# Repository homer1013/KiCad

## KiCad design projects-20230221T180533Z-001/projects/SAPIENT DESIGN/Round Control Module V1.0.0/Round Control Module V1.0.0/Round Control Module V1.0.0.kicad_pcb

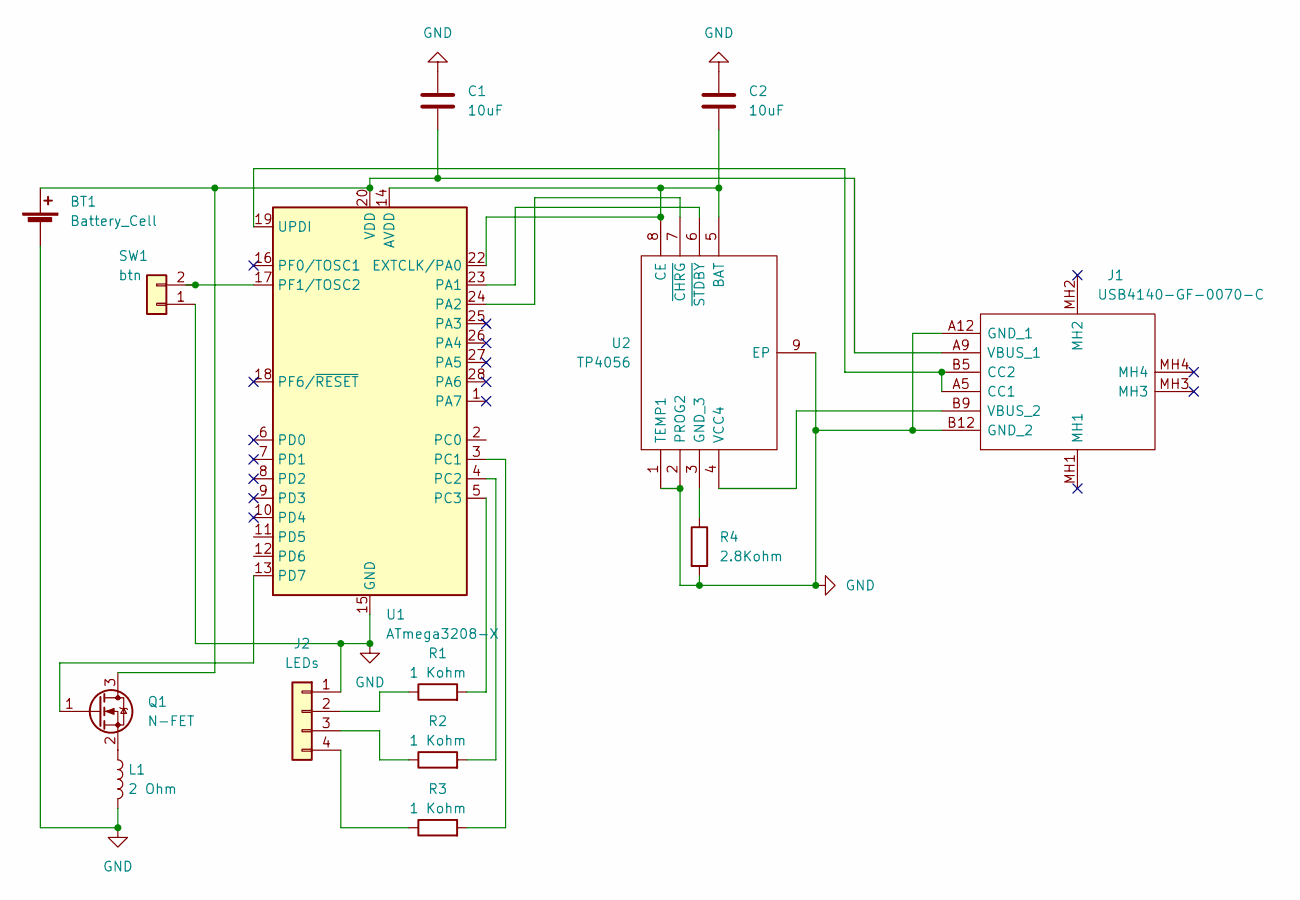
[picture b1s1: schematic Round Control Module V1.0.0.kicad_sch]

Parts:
BT1: Battery_Cell; PinHeader_1x02_P2.54mm_Vertical
C1, C2: 10uF; C_0603_1608Metric_Pad1.08x0.95mm_HandSolder
J1: USB4140-GF-0070-C; USB4140GF0070C; Mouser Part Number 640-USB4140-GF-0070C
J2: LEDs; PinHeader_1x04_P2.54mm_Vertical
L1: 2 Ohm; L_Axial_L6.6mm_D2.7mm_P2.54mm_Vertical_Vishay_IM-2
Q1: N-FET; SOT-23
R1, R2, R3: 1 Kohm; R_0603_1608Metric_Pad0.98x0.95mm_HandSolder
R4: 2.8Kohm; R_0603_1608Metric_Pad0.98x0.95mm_HandSolder
SW1: btn; PinHeader_1x02_P2.54mm_Vertical
U1: ATmega3208-X; SSOP-28_5.3x10.2mm_P0.65mm
U2: TP4056; SOIC-8-1EP_3.9x4.9mm_P1.27mm_EP2.514x3.2mm_ThermalVias; Manufacturer_Part_Number TP4056

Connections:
GND: BT1.2 (-), C1.1, C2.1, J1.A12 (GND_1), J1.B12 (GND_2), J2.1, L1.2, R4.2, SW1.1, U1.15 (GND), U1.21 (GND), U2.1 (TEMP1), U2.2 (PROG2), U2.9 (EP)
unnamed: BT1.1 (+), C1.2, J1.A9 (VBUS_1), Q1.3 (D), U1.20 (VDD)
unnamed: C2.2, U1.14 (AVDD), U1.22 (EXTCLK/PA0), U2.5 (BAT), U2.8 (CE)
unnamed: J2.2, R1.1
unnamed: J2.3, R2.1
unnamed: J2.4, R3.1
unnamed: L1.1, Q1.2 (S)
unnamed: Q1.1 (G), U1.13 (PD7)
unnamed: R1.2, U1.5 (PC3)
unnamed: R2.2, U1.4 (PC2)
unnamed: R3.2, U1.3 (PC1)
unnamed: R4.1, U2.3 (GND_3)
unnamed: SW1.2, U1.17 (PF1/TOSC2)
unnamed: J1.A5 (CC1), J1.B5 (CC2), U1.19 (UPDI)
unnamed: U1.23 (PA1), U2.6 (~STDBY)
unnamed: U1.24 (PA2), U2.7 (~CHRG)
unnamed: J1.B9 (VBUS_2), U2.4 (VCC4)

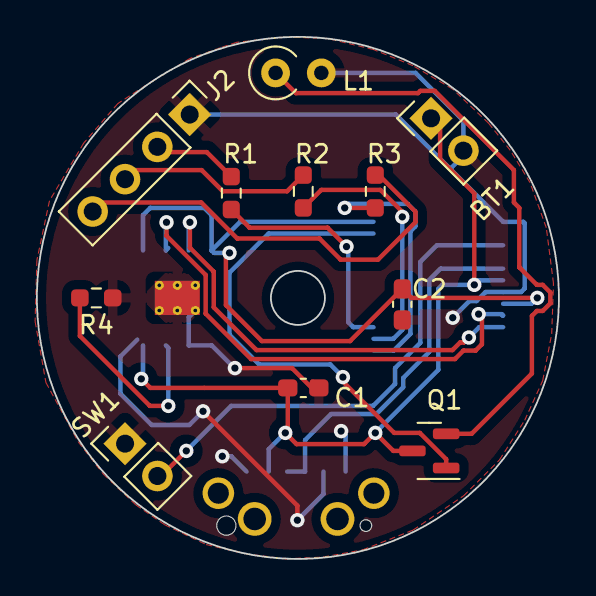
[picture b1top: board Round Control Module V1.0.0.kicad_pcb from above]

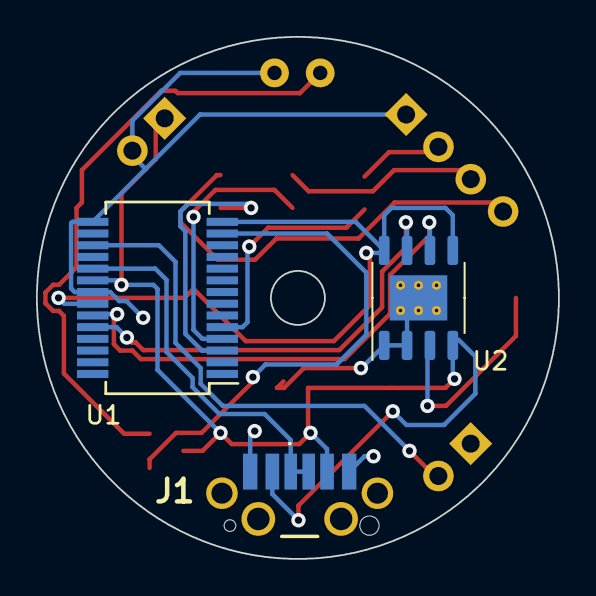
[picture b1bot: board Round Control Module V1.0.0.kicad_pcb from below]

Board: 2 copper layers, 29.0 x 29.0 mm, 14 parts (3 on the bottom side), 17 nets.

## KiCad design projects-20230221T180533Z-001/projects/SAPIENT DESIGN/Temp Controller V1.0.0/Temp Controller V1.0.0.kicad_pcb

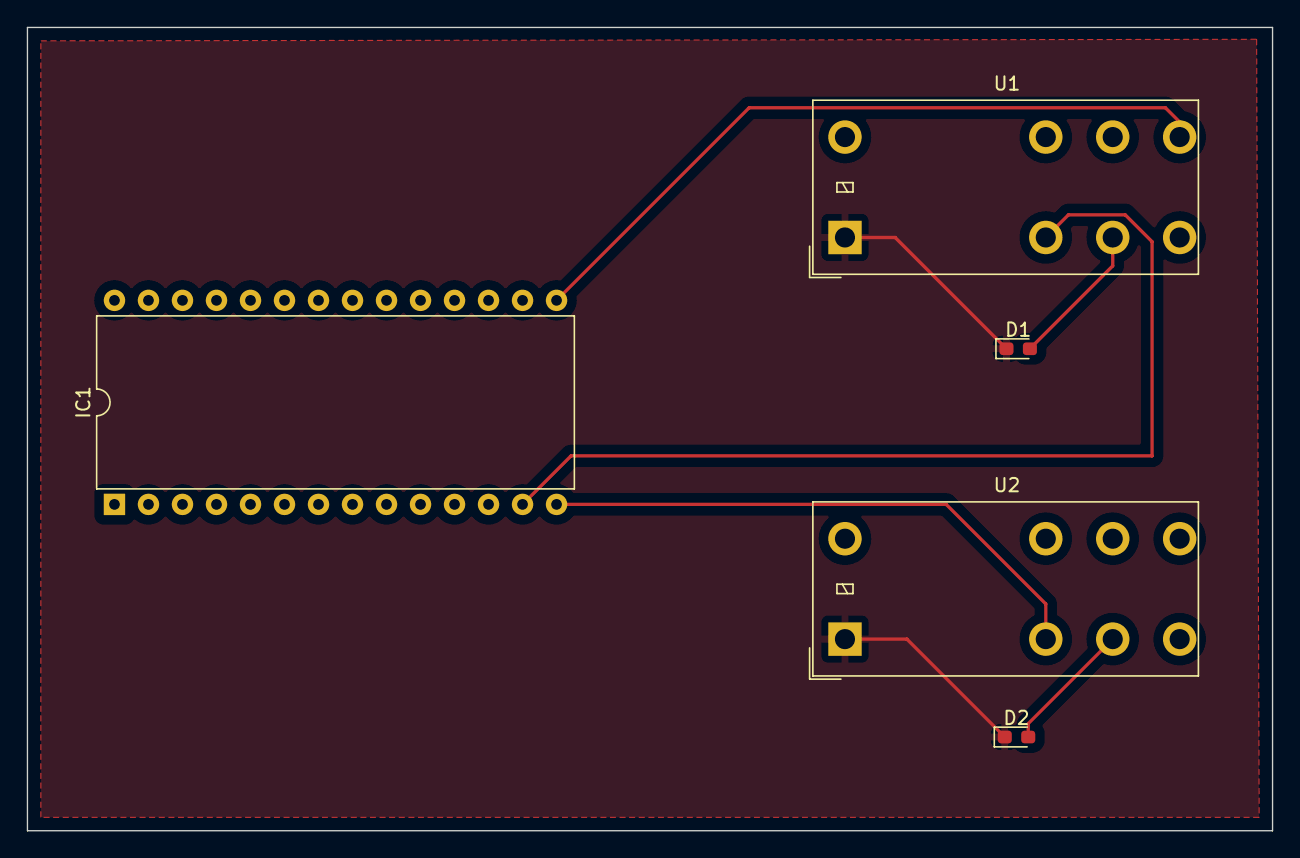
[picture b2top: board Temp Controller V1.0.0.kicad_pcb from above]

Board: 2 copper layers, 93.0 x 60.0 mm, 5 parts (0 on the bottom side), 6 nets.

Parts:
D1, D2: LED; LED_0603_1608Metric_Pad1.05x0.95mm_HandSolder
IC1: PIC18F27Q43-I_SP; DIP-28_W15.24mm
U1, U2: JS1A-12V-F; Relay_DPDT_Panasonic_JW2

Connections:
unnamed: IC1.13 (RC2), U1.2
unnamed: IC1.14 (RC3), U2.2
unnamed: IC1.15 (RC4), U1.5
unnamed: D1.2 (A), U1.3
unnamed: D1.1 (K), D2.1 (K), U1.1, U2.1
unnamed: D2.2 (A), U2.3
